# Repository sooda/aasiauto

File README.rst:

aASiauto
========

Aalto AS-0.3200 project work: control system and UI for a remote controlled
model car. Includes onboard car computer code for Atmel AVR microcontrollers
(originally Arduino sketches) with a proof-of-concept module for simulating all
this in Matlab, a PC-side UI for Matlab, and brake models in Simulink/Matlab.

http://sooda.dy.fi/2015/11/16/reliikki-7-8-rc-auton-ohjaustietokone-2013/

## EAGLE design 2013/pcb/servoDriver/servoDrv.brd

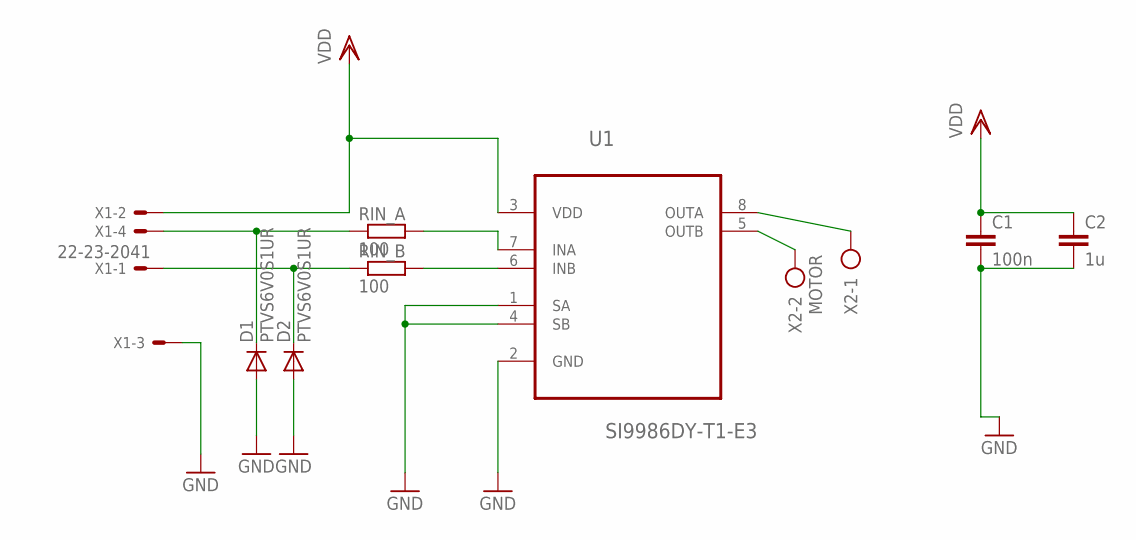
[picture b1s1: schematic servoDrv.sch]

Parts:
C1: 100n; C0805
C2: 1u; C0805
D1, D2: PTVS6V0S1UR; SOD123
RIN_A: 100; 0207/10
RIN_B: 100; 0207/10
U1: SI9986DY-T1-E3; SOIC127P600X175-8N
X1: 22-23-2041
X2: MOTOR; AK500/2

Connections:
GND: C1.2, C2.2, D1.A, D2.A, U1.1 (SA), U1.2 (GND), U1.4 (SB), X1.3
unnamed: U1.8 (OUTA), X2.1
unnamed: U1.5 (OUTB), X2.2
unnamed: D1.C, RIN_A.1, X1.4
unnamed: RIN_A.2, U1.7 (INA)
unnamed: RIN_B.2, U1.6 (INB)
unnamed: D2.C, RIN_B.1, X1.1
VDD: C1.1, C2.1, U1.3 (VDD), X1.2

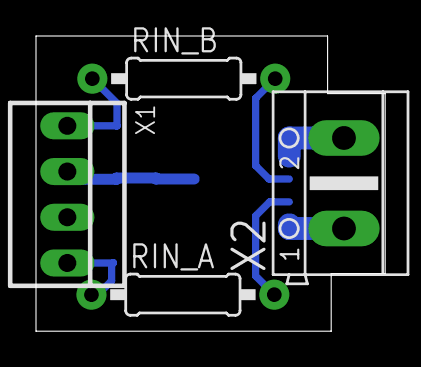
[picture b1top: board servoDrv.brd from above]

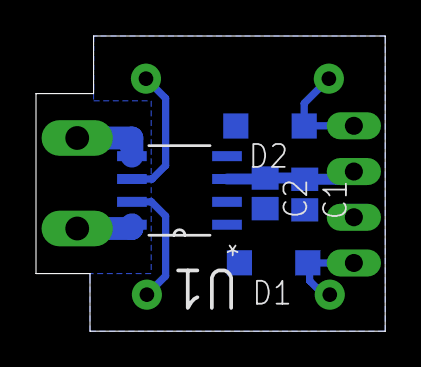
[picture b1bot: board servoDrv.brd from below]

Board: 2 copper layers, 19.4 x 16.4 mm, 9 parts (5 on the bottom side), 8 nets.

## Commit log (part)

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2013-09-23 Initial commit
    The original software from the last project in 2012.
2013-09-23 2012 project documentation, orig-software rename
2013-09-26 mekatroniikkaliite instrumentoinnista ja softasta
2013-09-26 kicad-tiedostot piirilevyistä
2013-09-29 suunnitelman alustava latex-puhtaaksikirjoitus
    vielä puuttuupi:
    - ajankäyttötaulukoiden viilaaminen
    - viittauksien fiksailu
    - yleinen oikoluku
    - riskinhallinta?
2013-09-29 plan: remove unused code commands
2013-09-29 Projektiplanin viilausta
2013-09-30 Lisätty sisällysluettelo ja poistettu sisennys kappaleiden alusta
2013-09-30 Poistettu sivunumero etusivulta
2013-09-30 aikatauluja vähän tarkemmiksi
2013-09-30 taulukkoreferenssit kuntoon
2013-09-30 Lisätty wikiin julkaistava projektisuunnitelma
2013-09-30 Lisätty projektisuunnitelman esityskalvot
2013-10-01 Brakecontrollerin debuggausohjelma. Vaatii vielä tietoliikenteen
2013-10-03 Lisätään korjattavan MATLAB GUIn pohja
2013-10-03 gui: Communication ja Logging luokat
2013-10-07 uusi main-komento jolla KäLi käynnistetään, koodin siistimistä
2013-10-08 lineaarinen kaksipyörämalli ajoneuvost a lisätty
2013-10-08 Poistettiin vanhoja apufunktioita
2013-10-08 gui: Jaettu callback funktioiden toiminnallisuutta eri tiedostoihin
2013-10-08 Lisätty sarjaporttilogia vanhasta järjestelmästä
2013-10-08 gui: Paranneltu auton parametrien tallennusta käyttöliittymässä
2013-10-08 Korjattu etumerkkivirheitä kaksipyörämallissa
2013-10-08 mex-testihässäkkä matlabille
    Esimerkkipohja siitä miten tuota mexiä käytetään, jotain tällaista voitaisiin
    käyttää itse kontrollerikoodille juttelemiseen. Kääntö matlabissa suoraan:
    mex controller.c program.c
    ja tulee controller-funktio käyttöön. Mexit ovat jotain normaaleja
    (plattakohtaisia) kirjastoja.
    Esimerkki ottaa 2-vektorin ja varastoi muistissa edellisen ja summaa ne.
2013-10-09 Lisätty kaksipyörämalliin sivuttaiskiihtyvyys-output
2013-10-18 lisätty *.gz .gitignore:en
2013-10-18 Vanhan järjestelmän debuggausta ja logeja
2013-10-18 vanhoojen softien toimintaa tutkittu, taskExcecutionTimes.ods:ssä dataa
2013-10-21 Implementoitu Car-luokan parametrien tallennus ja lataaminen
2013-10-26 poistettu jtn temppitiedostoja
2013-10-27 Väliraporttipresentaatio lisätty
2013-10-28 Välipresentaatiota päivitetty
2013-10-28 väliraporttitekstiä mikrokontrollereista ja raudasta
2013-10-28 Väliraportti googledocsista
2013-10-29 gui: appdata ja cardata Car-olioon
    Säilötään appdata ja cardata Car-olioon, jotta data voidaan
    helposti tallentaa parametrien yhteydessä.
    Lisätty ominaisuus, jolla Car-olio kutsutaan komennolla
    c = Car.getInstance;
    jolloin, cardataan ja appdataan päästään käsiksi kaikkialta
    c.appdata ja c.cardata struktuurien kautta.
2013-10-31 Lisätty Teensyn manuaalit
2013-11-06 Enkooderien datasheet lisätty
2013-11-06 Pyörintänopeuskoodausta Teensylle. Nopeus- ja kiihtyvyysdata bitshiftattu << 4
2013-11-06 servo-ohjaimen pcb:n ensimmäinen versio tehty
2013-11-06 servodriveriin tehty muutoksia. Sense-vastukset paremmin gnd-planeen.
2013-11-07 servodriverin skemaa muutettu, lisätty tvs:t inputteihin ja poistettu sense-vastukset. Myös puuttuvat viat lisätty.
2013-11-07 Lisää muutoksia servodriveriin, board outline lisätty.
2013-11-07 osalista servodriveriin
2013-11-07 farnellin ostoskori lisätty
2013-11-07 viimeisin versio servodriverista
2013-11-07 Usart -koodia aloitettu tekemään
2013-11-07 usart -kommunikaatiota. Makefile lisätty
2013-11-08 Koodia siistitty, tietorakenteet staattisiksi.
2013-11-08 Teensyn softan rakennetta hahmoteltu
2013-11-08 Teensyn koodiin lisätty 800Hz:n timer
2013-11-08 Makefile toimivaksi teensy.c:ssä muokattu ohjelmansuoritusflag:t usart.c:n rekisterit muokattu toimiviksi
2013-11-08 .gitignoreen lisätty eaglen temppi-filuja
2013-11-08 Teensyn softaa vielä muokkailtu
2013-11-08 Abs-koodia alettu hahmottelemaan
2013-11-08 structien miettimistä
2013-11-13 Lisätty ostoslista-excel Muokkailtu abs.h:ta
2013-11-13 abs.c:tä aloitettu
2013-11-15 kommentoitu implementoimattomat funktiot teensy.c:stä jotta kääntyy
2013-11-15 Lisätty initTeensy Makefileen ja otettu kommentit pois teensy.c:stä
2013-11-16 gui: kalman-suodin hahmotelma nopeuden ja kiihtyvyyden integroimiseksi
2013-11-16 gui: lasketaan paikka nopeuden perusteella
2013-11-16 abs-softaa mietitty, ja Teensyn inittiä
2013-11-27 gui: lisätty Kalman-filter GUIhin
2013-11-27 Päätietokoneen kommunikaatioframeworkkipohjasimu
    Tavuja eestaas matlabilta raaka-c-koodiin ja takaisin. Tähän sitten myös
    sekaan radiolinkki avr:n puolelle ja sarjaportti teensylle.
    Kommunikointiprotokolla toistaiseksi paketteja joiden muoto luokkaa
    [koko tyyppi (data)], ja joka luku 16-bittinen; skaalataan jossain
    myöhemmin (tm).
    Matlabin puolella parsitaan tavuvirtaa ja siitä paketti kerrallaan
2013-11-27 gui: Kommunikaation kehitystä soodan koodin pohjalta
2013-11-28 ABS-laskentaa implementoitu lisää
2013-11-28 Rengasmalli jarrutusvoiman laskentaa varten
2013-11-28 Dokumentaatiota abs-koodiin
2013-11-28 avr:n kommunikaation hahmottelua, ei testattu viel
2013-11-28 edioitu soodan communikaatioluokkia
2013-11-28 gui: otettu uusi protokolla käyttöön (kesken)
2013-11-28 ringbuf-testi ja pari bugifiksiä copypasteista
2013-11-29 Abs-koodia muokattu, parametrien muuttaminen ja hakeminen lisätty, vehicle.c vain testausta varten
2013-11-29 gui: Uuden protokollan käyttöönotto ja demo-mode esitystä varten
2013-11-29 gui: poistettiin ylimääräisiä tiedostoja..
2013-11-30 Lopppupreenstaatiopohja olemassa
2013-12-01 massiivinen frameworkin alkupuuhastelu
    lisää bufferisettiä, ringbuf käyttöagnostiseksi ja uartbuf
    sarjaporteille; testattu omalla teensyllä pikaisesti. pingpongit ok.
    yleisen koodin voisi säätää käytettäväksi joka kontrollerilla; sama
    kommunikointimekanismi kaikille vähentää copypastaa. uarttien indeksit,
    pwm-rekisterit yms. konffiheaderiin.
2013-12-01 alkuperäiset pwm-konffit
2013-12-01 Loppupresentaatioon kirjoitettu ABS- ja ESC-järjestelmistä
2013-12-01 gui: Korjattu protokollaa ja näppäimistön lukua
    - Protokollaan lisätty viestin alkutavu 0xFF
    - Näppäimistöä luetaan Matlabin omilla funktioilla
    -> ulkopuolisia kirjastoja ei tarvita
    TODO: Viestidatasta pitää vielä monistaa siitä löytyvät
    0xFF tavut.
2013-12-01 Abs- ja esp-koodia
2013-12-01 purkkaa pääkontrollerille
    oikea uart käyttöön, muutamien porttien suunnat, ajovalot testiksi
2013-12-01 gui: protokollan hieromista ja koodin siistimistä
2013-12-01 lisää pääohjelmatavaraa
    täähän alkaa saada jotain muotoa jo. työtimerit ja mittausten lähetys
    sekä raportointi-id:t jne.
2013-12-01 nope, ei mittausdatassa eofia pitänytkään olla
2013-12-01 off by 2x
2013-12-01 pyyttontyökalu mittausdatafloodin katseluun
2013-12-01 gui: Lisätty uudet ABS parametrit käliin
2013-12-01 gui: parametrien tiedostoontallennus
2013-12-01 ad-muunnin
2013-12-01 off-by-1 meas nitems
2013-12-01 jarruservojen sijainnit ovat hassusti
2013-12-01 jarrut: modulaarisuutta ja lokaalia purkkahackia
    viestit pc -> driver -> braker toimii, jarruservot pyörii
2013-12-01 gui: poistettu joku turha p*ska
2013-12-01 gui: Fiksailtu tiedostoontallennusta ja semmottii
2013-12-01 such modularity, so debug. many stream. wow.
2013-12-02 teensy mukaan leikkiin
    nyt tuntuisi data kulkevan teensyltä aina pc-hostille asti.
    jarrukontrollerillakin on nyt debuggiportti.
    TODO: oikeastaan mittaa ne renkaiden nopeudet... placeholderit pois, ja
    päivitysnopeuksia ylemmäs (ledien välkkymisen erottaa paremmin näillä
    pienemmillä taajuuksilla)
2013-12-02 wheelspeed-koodit teensyyn mukaan
    Teensy oikeastaan lukemaan niitä mittauksia. TODO: katso että nimet ovat
    oikein; säädä enkooderit juttelemaan 2048 pulssia kierrokselta sen 512
    sijaan. Liukuva keskiarvo olisi kiva jos haluttas nopeammin mittauksia.
    Luvut ovat joka tapauksessa niin pieniä (luokkaa 10 kun käsin
    pyörittää), että kannattaisi varmaan palauttaa viimeisten N mittauksen
    summa eikä keskiarvoa.
2013-12-02 gui: Korjattu protokollakommunikointia
    - Ajetaan "yhdessä säikeessä"
    - Lisätty pingaus 100ms välein
    - Luetaan & parsitaan dataa myös vaikka manualdrive ei ole
    aktivoituna (TODO: check me)
    TODO: ihmettele miksi jännitteiden plottaaminen ei toimi
2013-12-02 loppuraporttiin mikrokontrolleriosuutta
2013-12-02 loppuraportti: puljasin GUI:sta pari palloa lisää
2013-12-02 presis: demomode.png
2013-12-02 raporttiin kuvia ja hiomista
2013-12-02 .. ja raportin kuvat myös
2013-12-02 Lisätty presentaatioon kuvia ESP:stä ja ABS:stä
2013-12-02 Nuoli poistettu ESP-kalvosta
2013-12-02 paskaa
2013-12-02 Lisätty kuvaaja
2013-12-02 kuvei
2013-12-02 gui: renkaiden pyörimisnopeuksien tuonti
2013-12-02 ABS-koodia tehty lisää.
2013-12-02 typo
2013-12-02 ABS-kodiin lisätty pwm-ohjaukset jarruille
2013-12-02 jarruparametrien tallennus ja raportointi
    ping pong pang kauheeta eestaas palloilua, voi kun oisivat väylässä.
    parametrit driverin läpi jarruohjaimelle ja takaisin; servoille
    eepromiin tallennus niin että nollakohdat jopa muistetaan.
2013-12-02 watchdog. pingit, pakko ottaa
    stoppaa viestien lähettäminen ja ajaminen jos pingiä ei ole hetkeen
    (esim. puoli sekuntia) tullut
2013-12-02 gui: parametrien luku autolta
2013-12-02 servon pinnikonffit oli kadonnu johonki
2013-12-02 copypastetypoja jarruservoista pois
2013-12-02 servot tottelemaan rajoja ohjauksessakin
2013-12-02 gui: Korjattiin kalman-filtteri
2013-12-03 NÄILLÄ LIIKKUU
2013-12-05 gui: Pohjaa automaattiajolle
2013-12-05 Muutettu servoDriver pcb yksipuoleiseksi
2013-12-05 Pieniä muutoksia servo pcb:hen Servojen H-sillan manuaali lisätty
2013-12-06 Simulink-mallin päivitystä
2013-12-06 simulinkkausta
2013-12-07 gui: koodin siistimistä
2013-12-07 gui: Liukuhihna-ajo
2013-12-07 Toimivampi abs simulaatio
2013-12-07 ABS-mallin päivitys
2013-12-08 poistettu turhhia tiedostoja
2013-12-12 docs: kuvia loppuraporttiin
2013-12-13 mcu: yhtenäisempi mainloop, ledit, keepalive
    - virheeseen lähettäjäid
    - pongiin lähettäjäid
    - keepalive-watchdog kaikille
    - selkeämmät henkiledivilkut
2013-12-13 gitignore elf hex tags
2013-12-13 mcu: siivousta; vanha roska pois ja uutta tilalle
2013-12-13 mitähän nää randomit jumitukset on
2013-12-13 jotain pahaa tässä nyt on kun tavuja putoilee
2013-12-13 Lisää simulinkkaamista
2013-12-13 Ja mallin tallennus
2013-12-13 lisätty uusi kuva loppudokkariin
2013-12-13 Simulinkkiä päivitetty
2013-12-14 doc: lisätty jakauma
2013-12-14 lisätty puuttuva filu
2013-12-14 näppiskäsittelyn vektorinloppubugifix
2013-12-14 linuxin /dev/ttyUSBit guivalikkoon
2013-12-14 as-labran jysinohjeet: tkk.cam
2013-12-15 loppuraportti latextex-muotoiseksi docsista
    vielä vaatii viilausta ja muutamia muutoksia
2013-12-15 simulinkkauksia
2013-12-15 Loppudokumentaatiota, liitteitä lisätty ja esp:stä kirjoitettu lisää
2013-12-15 oikean kokoiset deltat loppuraporttiin
2013-12-15 loppudokkariin fiksejä
2013-12-15 Teensy-kappale dokkariin
2013-12-15 parametritaulukko docsista liitteeksi raporttiin
2013-12-15 paperikansilehti erikseen ja titlesivu taviksille
2013-12-15 vanha turha loki pois
2013-12-15 avr-puolen koodin rakenne dokkariin
2013-12-15 suuri avr-koodin refaktorointi ja siistintä
    - yhteisiä juttuja yhteisiksi; vähemmän copypastaa
    - loogisempia paikkoja muutamille funktioille
    - nimeämiskäytäntö paremmaksi paikoittain
    - vanhaa mössöä pois
2013-12-15 java.opts linuximatlabia varten, sarjaportit ok
2013-12-15 core.c oikean nimiseksi
2013-12-15 matlabdokumentaatiota simuintegraatiosta
2013-12-15 matlabsimulaatio ajan tasalle, komentorivimoodikin
    renkaiden nopeus feikataan moottorisyötteestä ja rattipotikka ratista
2013-12-15 gui: enabloidaan simulointi
2013-12-15 ringbuftestille tuki taas
2013-12-15 viime hetken wtf:t pois
2013-12-15 gui twiikkausta, korjattiin simulaation alustusta
2013-12-15 asddsa
2013-12-15 uusi jakauma
2013-12-15 dokkarin avr-tiedostot ajan tasalle
2013-12-15 parametrien defaultit
2013-12-15 ajankäyttö-excel
2013-12-15 dokkari finaaliin; tunnit kuntoon, pari puutefixiä
2013-12-15 ... ja bugisäätö
2015-11-15 vanhat turhat dokkarit pois
2015-11-15 siirrä vanha readme
